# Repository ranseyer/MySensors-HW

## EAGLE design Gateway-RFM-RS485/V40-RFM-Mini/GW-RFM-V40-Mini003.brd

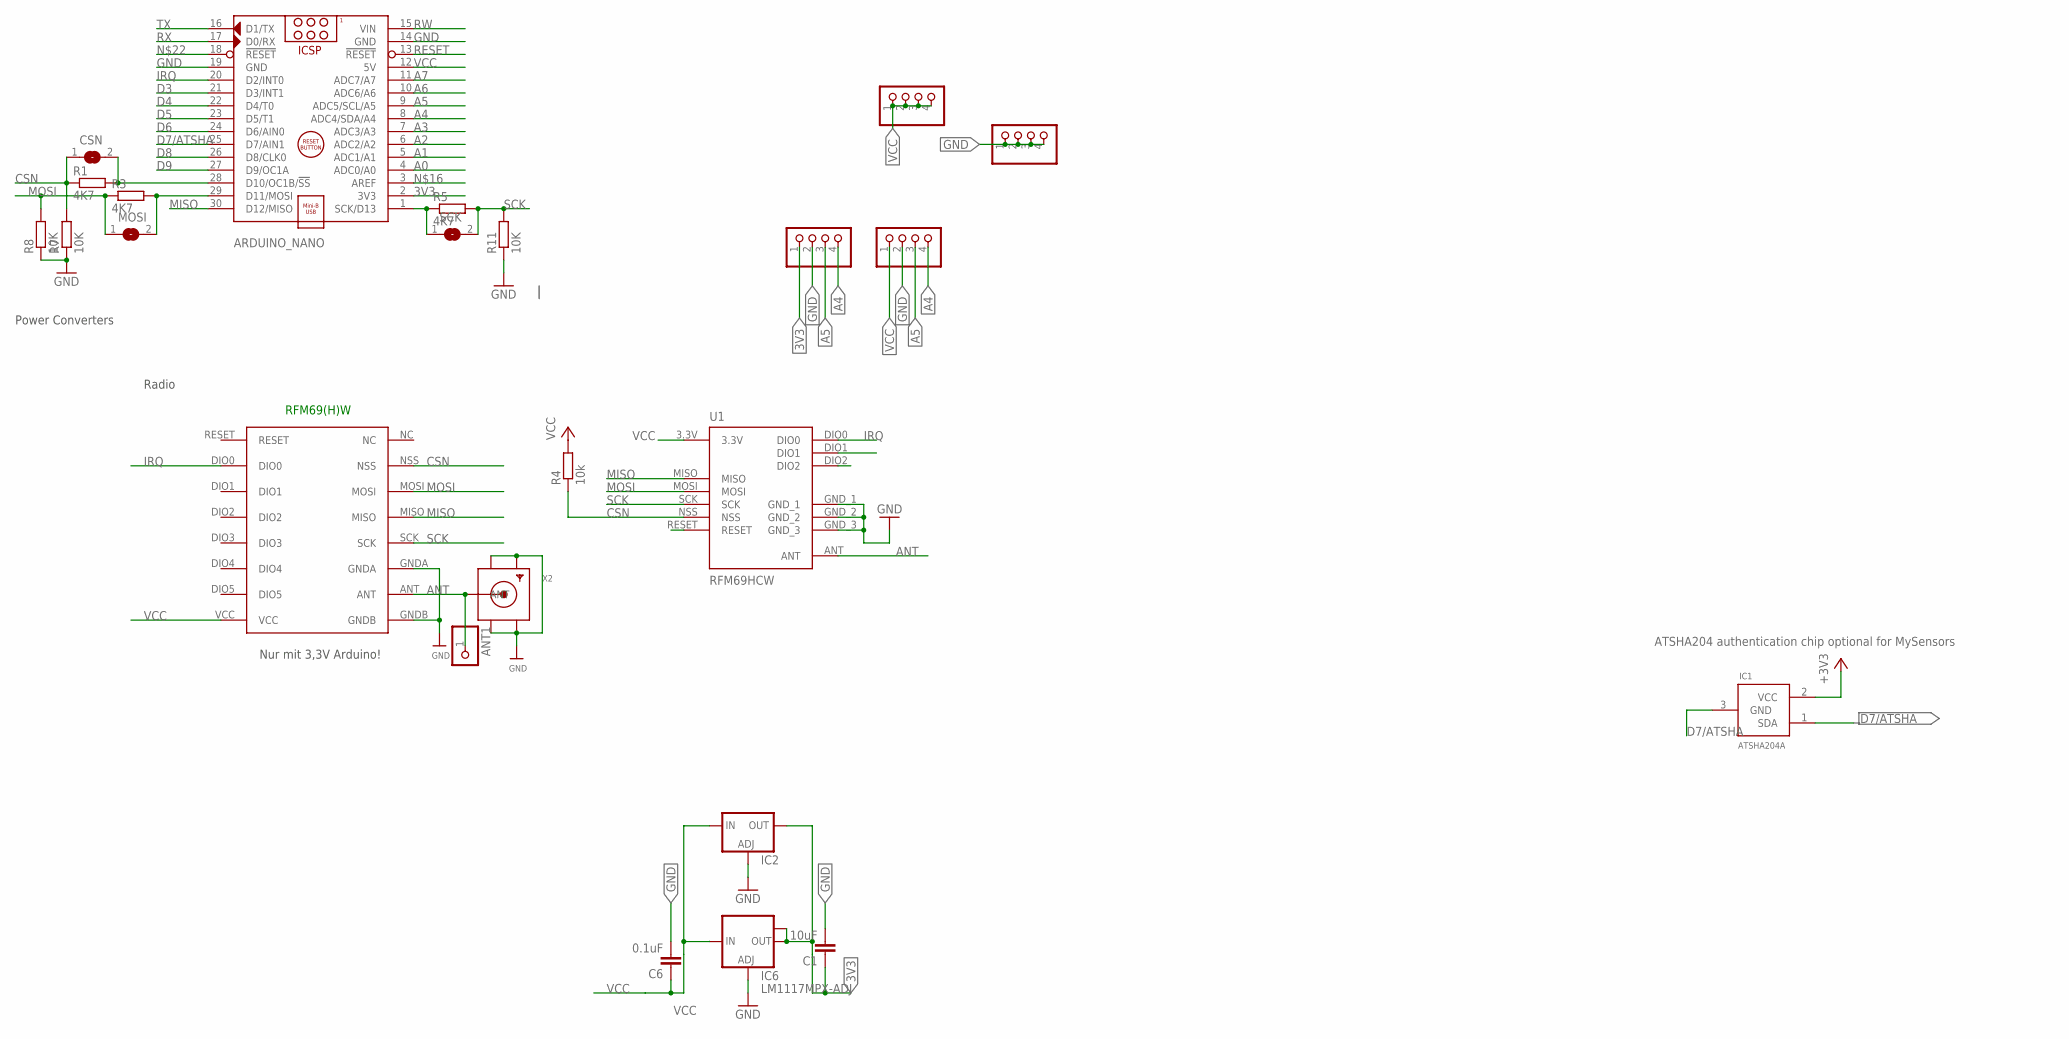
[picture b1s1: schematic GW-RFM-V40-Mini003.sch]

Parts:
ANT1: PINHD-1X1; 1X01
ARDUINO_NANO: ARDUINO_NANO_OHNE-BOHR; ARDUINO_NANO
C1: 10uF; C1210
C6: 0.1uF; C1206
CSN: SJ
IC1: ATSHA204A; SOT23
IC2: LD117ADT50TR; DPACK
IC6: LM1117MPX-ADJ; SOT223
JP1, JP3, JP17, JP18: PINHD-1X04_2.54-S; 1X04-S
MOSI: SJ
R1, R3, R5: 4K7; M0805
R4: 10k; M0805
R7, R8, R11: 10K; M0805
RFM69W: RFM69HW; RFM
SCK: SJ
U1: RFM69HCW; RFM69HCW-XXXS2
X2: SMACONNECTOR_EDGE; SMA_EDGELAUNCH

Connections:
3V3: ARDUINO_NANO.2 (3V3), C1.1, IC2.4 (OUT), IC6.2 (OUT), IC6.TAB (OUT1), JP17.1
A0: ARDUINO_NANO.4 (ADC0/A0)
A1: ARDUINO_NANO.5 (ADC1/A1)
A2: ARDUINO_NANO.6 (ADC2/A2)
A3: ARDUINO_NANO.7 (ADC3/A3)
A4: ARDUINO_NANO.8 (ADC4/SDA/A4), JP17.4, JP18.4
A5: ARDUINO_NANO.9 (ADC5/SCL/A5), JP17.3, JP18.3
A6: ARDUINO_NANO.10 (ADC6/A6)
A7: ARDUINO_NANO.11 (ADC7/A7)
ANT: ANT1.1, RFM69W.ANT, U1.ANT, X2.P (ANT)
CSN: CSN.1, R1.1, R4.1, R7.2, RFM69W.NSS, U1.NSS
D3: ARDUINO_NANO.21 (D3/INT1)
D4: ARDUINO_NANO.22 (D4/T0)
D5: ARDUINO_NANO.23 (D5/T1)
D6: ARDUINO_NANO.24 (D6/AIN0)
D7/ATSHA: ARDUINO_NANO.25 (D7/AIN1), IC1.1 (SDA), IC1.3 (GND)
D8: ARDUINO_NANO.26 (D8/CLK0)
D9: ARDUINO_NANO.27 (D9/OC1A)
GND: ARDUINO_NANO.14 (GND), ARDUINO_NANO.19 (GND), C1.2, C6.2, IC2.1 (ADJ), IC6.1 (ADJ), JP1.1, JP1.2, JP1.3, JP1.4, JP17.2, JP18.2, R7.1, R8.1, R11.1, RFM69W.GNDA, RFM69W.GNDB, U1.GND_1, U1.GND_2, U1.GND_3, X2.GND@1 (GND4), X2.GND@2 (GND3), X2.GND@3 (GND2), X2.GND@4 (GND1)
IRQ: ARDUINO_NANO.20 (D2/INT0), RFM69W.DIO0, U1.DIO0
MISO: ARDUINO_NANO.30 (D12/MISO), RFM69W.MISO, U1.MISO
MOSI: MOSI.1, R3.1, R8.2, RFM69W.MOSI, U1.MOSI
unnamed: ARDUINO_NANO.1 (SCK/D13), R5.1, SCK.1
unnamed: ARDUINO_NANO.28 (D10/OC1B/!SS), CSN.2, R1.2
unnamed: ARDUINO_NANO.29 (D11/MOSI), MOSI.2, R3.2
RESET: ARDUINO_NANO.13 (!RESET)
RW: ARDUINO_NANO.15 (VIN)
RX: ARDUINO_NANO.17 (D0/RX)
SCK: R5.2, R11.2, RFM69W.SCK, SCK.2, U1.SCK
TX: ARDUINO_NANO.16 (D1/TX)
VCC: ARDUINO_NANO.12 (5V), C6.1, IC1.2 (VCC), IC2.3 (IN), IC6.3 (IN), JP3.1, JP3.2, JP3.3, JP3.4, JP18.1, R4.2, RFM69W.VCC, U1.3.3V

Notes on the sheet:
RFM69(H)W
Nur mit 3,3V Arduino!
Radio
ATSHA204 authentication chip optional for MySensors
Power Converters

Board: 2 copper layers, 24 parts (17 on the bottom side), 15 nets, no tracks yet.

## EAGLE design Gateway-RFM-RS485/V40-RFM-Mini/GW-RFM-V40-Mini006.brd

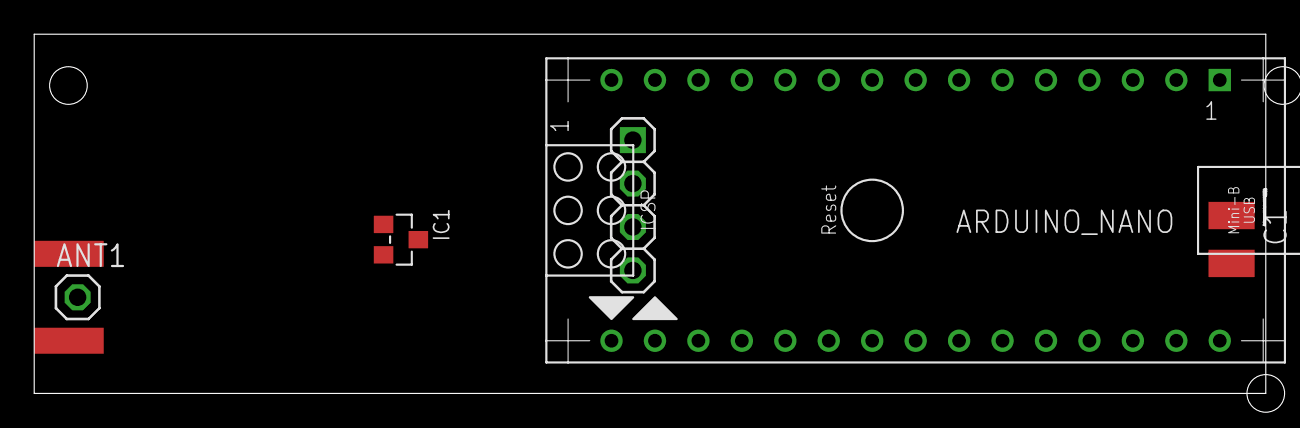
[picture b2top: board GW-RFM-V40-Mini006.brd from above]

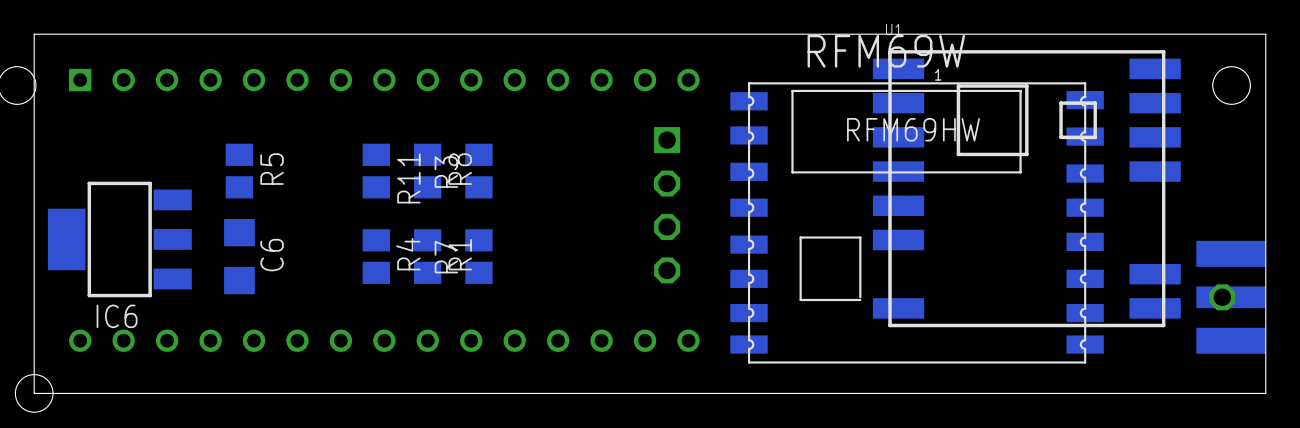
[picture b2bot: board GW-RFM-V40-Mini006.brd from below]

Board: 2 copper layers, 72.0 x 21.0 mm, 17 parts (12 on the bottom side), 15 nets, no tracks yet.

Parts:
ANT1: 1X01
ARDUINO_NANO: ARDUINO_NANO
C1: 10uF; C1210
C6: 0.1uF; C1206
IC1: ATSHA204A; SOT23
IC6: LM1117MPX-ADJ; SOT223
JP17: 1X04-S
R1, R3, R5: 4K7; M0805
R4: 10k; M0805
R7, R8, R11: 10K; M0805
RFM69W: RFM69HW; RFM
U1: RFM69HCW; RFM69HCW-XXXS2
X2: SMA_EDGELAUNCH

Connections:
3V3: ARDUINO_NANO.2, C1.1, IC6.2, IC6.TAB, JP17.1
A4: ARDUINO_NANO.8, JP17.4
A5: ARDUINO_NANO.9, JP17.3
ANT: ANT1.1, RFM69W.ANT, U1.ANT, X2.P
CSN: R1.1, R4.1, R7.2, RFM69W.NSS, U1.NSS
D7/ATSHA: ARDUINO_NANO.25, IC1.1, IC1.3
GND: ARDUINO_NANO.14, ARDUINO_NANO.19, C1.2, C6.2, IC6.1, JP17.2, R7.1, R8.1, R11.1, RFM69W.GNDA, RFM69W.GNDB, U1.GND_1, U1.GND_2, U1.GND_3, X2.GND@1, X2.GND@2, X2.GND@3, X2.GND@4
IRQ: ARDUINO_NANO.20, RFM69W.DIO0, U1.DIO0
MISO: ARDUINO_NANO.30, RFM69W.MISO, U1.MISO
MOSI: R3.1, R8.2, RFM69W.MOSI, U1.MOSI
unnamed: ARDUINO_NANO.1, R5.1
unnamed: ARDUINO_NANO.28, R1.2
unnamed: ARDUINO_NANO.29, R3.2
SCK: R5.2, R11.2, RFM69W.SCK, U1.SCK
VCC: ARDUINO_NANO.12, C6.1, IC1.2, IC6.3, R4.2, RFM69W.VCC, U1.3.3V

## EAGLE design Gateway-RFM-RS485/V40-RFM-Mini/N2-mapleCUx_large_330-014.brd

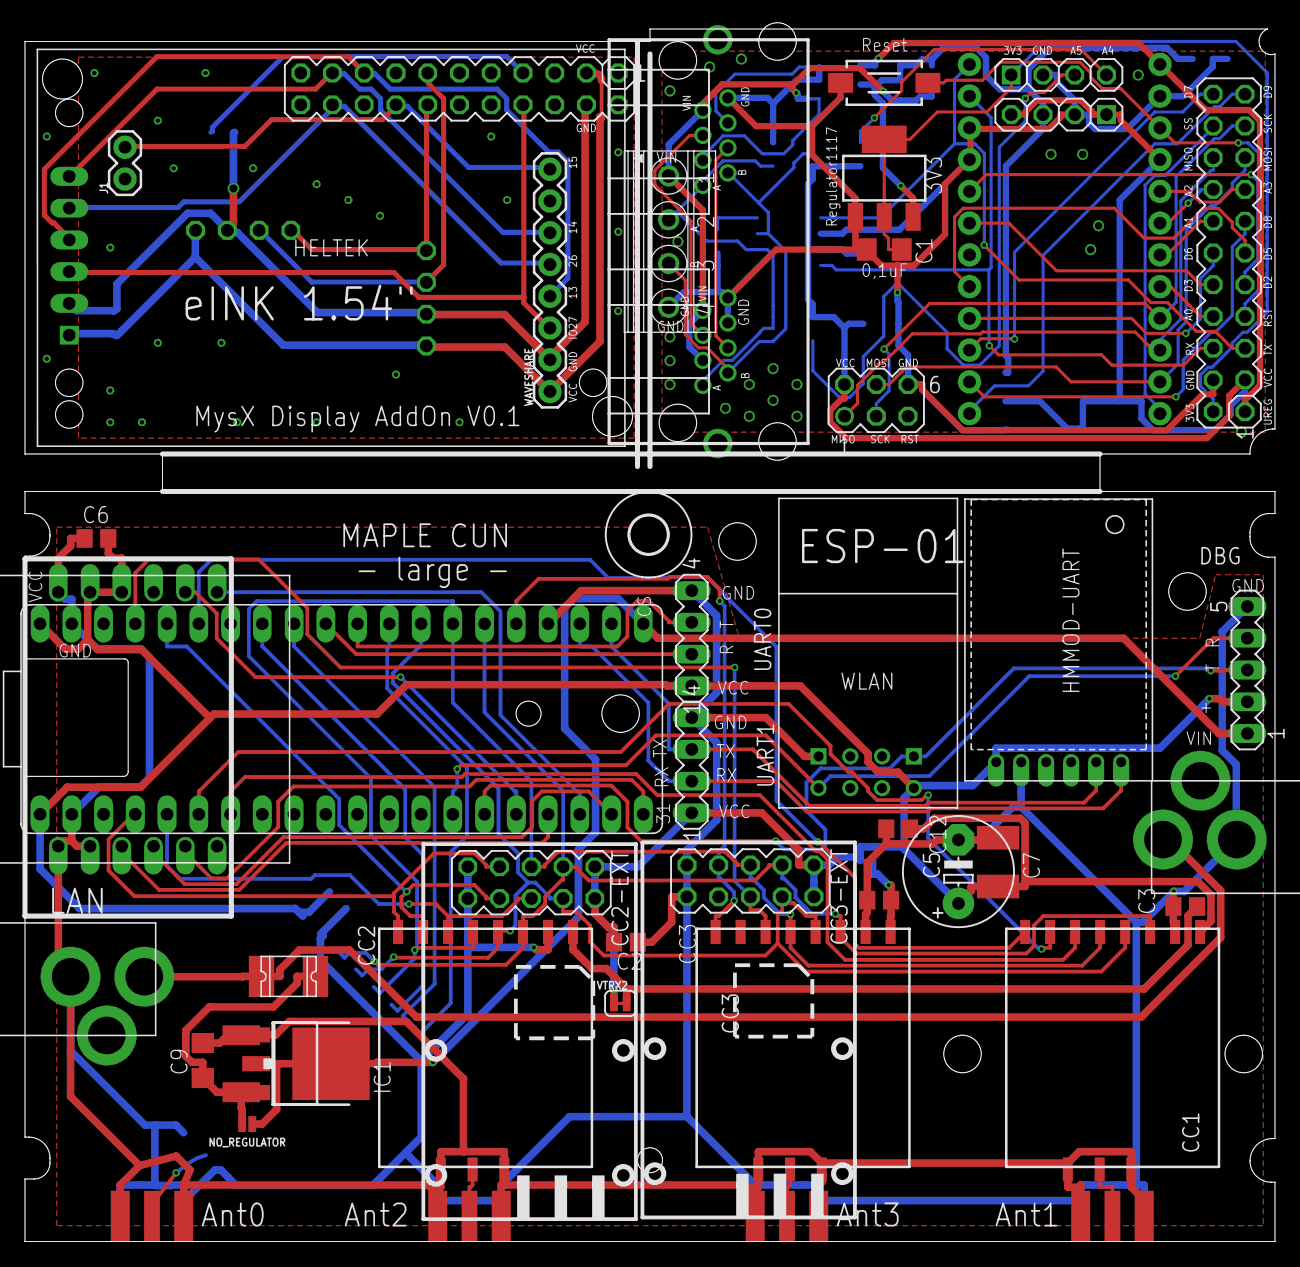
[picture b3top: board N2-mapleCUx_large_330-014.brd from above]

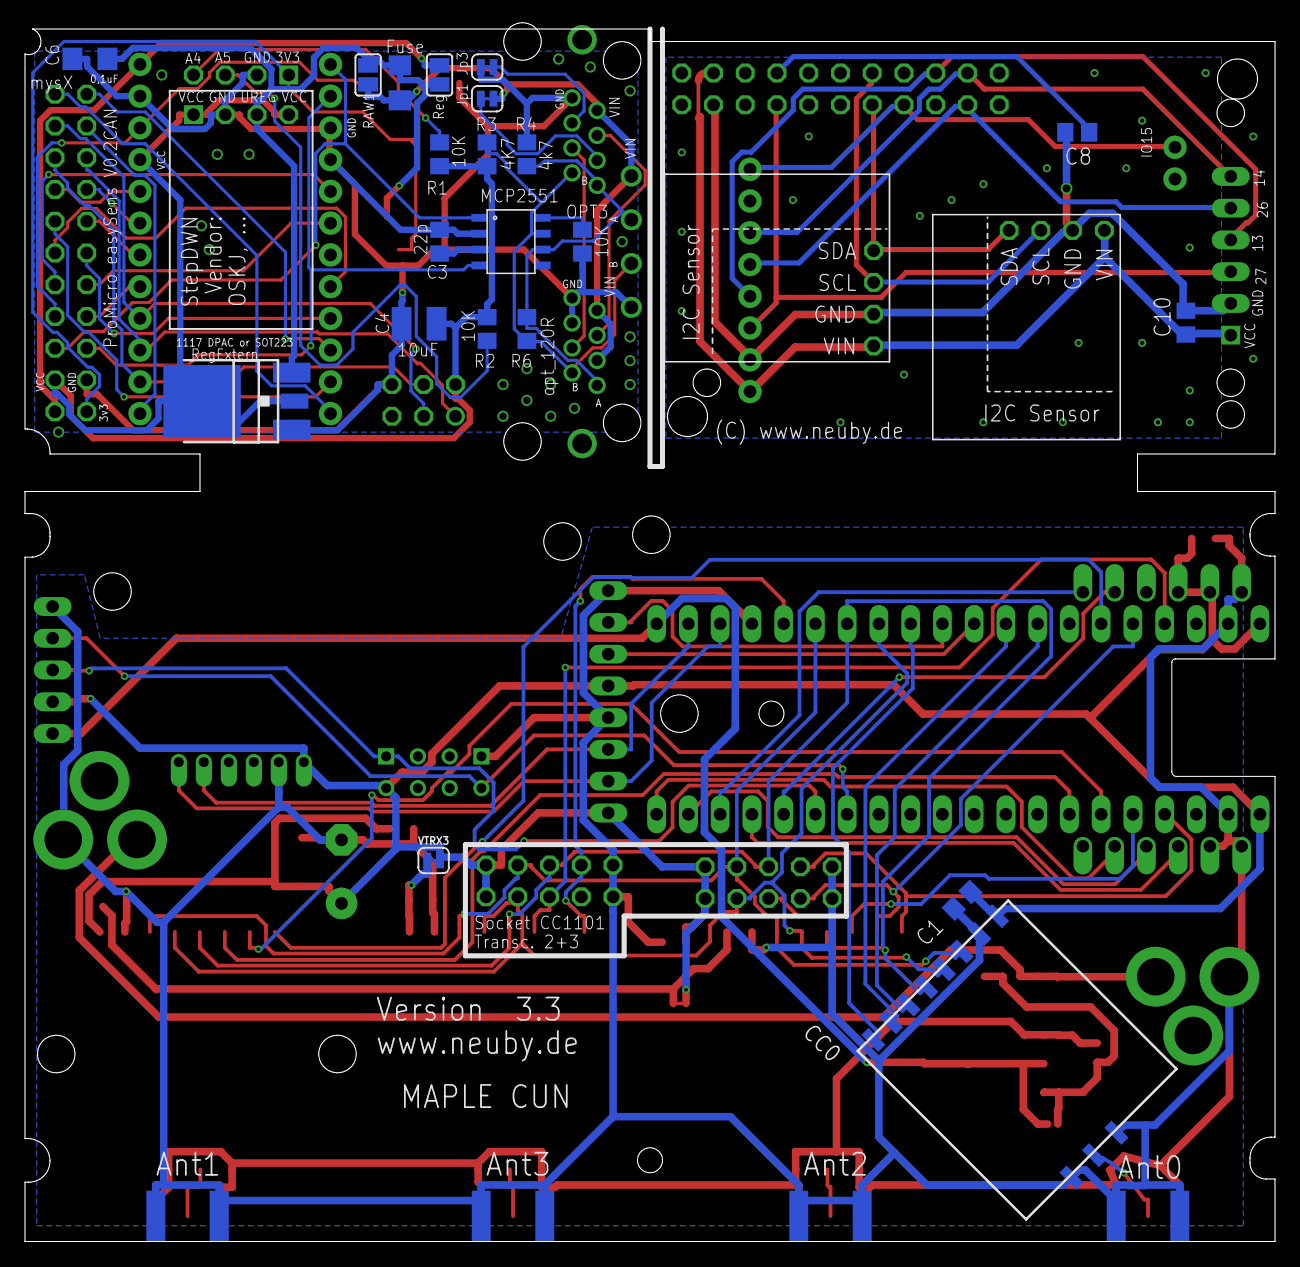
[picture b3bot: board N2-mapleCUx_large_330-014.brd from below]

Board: 2 copper layers, 100.0 x 97.0 mm, 70 parts (24 on the bottom side), 79 nets.

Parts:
B1: SPARKFUN_PRO_MICRO
C1, C2, C3, C4, C6, C12: 22pF; C0805
C5: 220uF; E5-8,5
C7: C1812
C8: 2u2; C0805
C9, C14, C15: 0.1uF; C1206
C10: 22u; C0805
C11: 22p; C0805
C13: 10uF; C1210
CC0: CC1101; CC1101_MODULE1_SMD
CC1, CC2, CC3: CC1101_MODULE1SMD; CC1101_MODULE1_SMD
CC2-EXT, CC3-EXT: CC1101_MODULE3_DIL
DBG: MA05-1
F1: 1812L
F2: 6V/0.75A; 1206
FLASH: DTSM-3
H6: MOUNT-HOLE3.0; 3,0
HELTEK: HELTEC_1.54STANDARD1; HELTEC_1.54INCH
HMMOD-UART: HM-MOD-UARTDIL; HM-MOD-UART-DIL
I2C: 1X04-S
IC1, IC3: LD117ADT50TR; DPACK
IC2: LAN-USR-ES1; USR-ES1
IC4, IC5, IC6: LM1117MPX-ADJ; SOT223
J1: 1X02
J4: RJ45_2X_S
JP1, JP3: JUMPER-SMT_2_NC_TRACE_SILK; SMT-JUMPER_2_NC_TRACE_SILK
MYSX: MA11-2
NO_REGULATOR: JUMPER-SMT_2_NC_PASTE_NO-SILK; SMT-JUMPER_2_NC_PASTE_NO-SILK
OPT3: 10K; R0805
R1, R2: 10K; R0805
R3: 4K7; R0805
R4: 4k7; R0805
R6: 120R; R0805
RAW1: SJ
REG_BRIDGE: SJ
STEPDWN: 1X04-S
SV1: MA03-2
SV2: MA11-2
U$1: MAPLEMINI; 20-DIP
U$2, U$3: 2.1MMJACKTHM; PJ-102A
U$4, U$5: I2C-BREAKOUT; I2C_BREAKOUT
U$6: MCP2551; SOIC-8
UART0, UART1: MA04-1
VTRX2, VTRX3: JUMPER-SMT_2_NC_TRACE_SILK; SMT-JUMPER_2_NC_TRACE_SILK
WAVESHARE: 1X08
WLAN: ESP01
X1, X2, X3, X5: SMA_EDGELAUNCH
X4: 1751264

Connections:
1: J4.1-3, JP1.1
2: J4.1-6, JP3.1
3V1: C15.2, I2C.1, IC5.2, IC5.TAB, SV2.2
A: J4.1-1, J4.2-1, R4.1, R6.2, U$6.CANL, X4.2
A0: B1.17, SV2.8
A1: B1.18, SV2.14
A2: B1.19, SV2.16
A3: B1.20, SV2.15
A4: I2C.4, R1.2
A5: I2C.3, R2.2
ANT0: CC0.ANT, X5.P
ANT1: CC1.ANT, X1.P
ANT2: CC2.ANT, X2.P
ANT3: CC3.ANT, X3.P
B: J4.1-2, J4.2-2, R3.2, R6.1, U$6.CANH, X4.3
CANH: J4.1-4, J4.2-4
CANL: J4.1-5, J4.2-5
CC_CS0: CC0.CSN, U$1.29
CC_CS1: CC1.CSN, U$1.35
CC_CS2: CC2.CSN, CC2-EXT.CSN, U$1.4
CC_CS3: CC3.CSN, CC3-EXT.CSN, U$1.25
CC_IN_0: CC0.GDO2, U$1.33
CC_IN_1: CC1.GDO2, U$1.7
CC_IN_2: CC2.GDO2, CC2-EXT.GDO2, U$1.5
CC_IN_3: CC3.GDO2, CC3-EXT.GDO2, U$1.37
CC_OUT_0: CC0.GDO0, U$1.32
CC_OUT_1: CC1.GDO0, U$1.6
CC_OUT_2: CC2.GDO0, CC2-EXT.GDO0, U$1.36
D2: B1.5, SV2.9
D3: B1.6, SV2.10
D5: B1.8, SV2.11
D6: B1.9, SV2.12
D7: B1.10, SV2.22
D8: B1.11, SV2.13
D9: B1.12, SV2.21
D10_SS: B1.13, SV2.20
D11_MOSI: B1.14, SV1.4, SV2.17
D12_MISO: B1.15, SV1.1, SV2.18
D13_SCK: B1.16, SV1.3, SV2.19
EN: C8.1, MYSX.7
GND: C1.1, C2.1, C3.1, C4.1, C5.-, C6.2, C7.1, C9.2, C12.2, CC0.GND@0, CC0.GND@1, CC0.GND@2, CC1.GND@0, CC1.GND@1, CC1.GND@2, CC2.GND@0, CC2.GND@1, CC2.GND@2, CC2-EXT.GND@0, CC2-EXT.GND@1, CC3.GND@0, CC3.GND@1, CC3.GND@2, CC3-EXT.GND@0, CC3-EXT.GND@1, DBG.5, HMMOD-UART.2, IC1.1, IC2.1, IC2.2, IC2.12, IC6.1, U$1.2, U$1.24, U$1.39, U$2.RING, U$3.RING, UART0.4, UART1.4, WLAN.GND, X1.GND@1, X1.GND@2, X1.GND@3, X1.GND@4, X2.GND@1, X2.GND@2, X2.GND@3, X2.GND@4, X3.GND@1, X3.GND@2, X3.GND@3, X3.GND@4, X5.GND@1, X5.GND@2, X5.GND@3, X5.GND@4
GND1: C8.2, C10.2, HELTEK.GND, MYSX.4, U$4.GND, U$5.GND, WAVESHARE.2
GND2: B1.3, B1.4, B1.23, C11.1, C13.2, C14.2, C15.1, FLASH.1, I2C.2, IC3.1, IC4.1, IC5.1, J4.1-8, J4.2-6, J4.2-8, JP3.2, OPT3.1, R4.2, STEPDWN.2, SV1.6, SV2.4, U$6.VSS, X4.4
IN: C9.1, F1.P$1, IC1.3, IC6.3, NO_REGULATOR.2
IN1: F2.2, J4.1-7, J4.2-3, J4.2-7, JP1.2, RAW1.1, X4.1
IO13: HELTEK.SDI, MYSX.17, WAVESHARE.4
IO14: HELTEK.CLK, MYSX.19, WAVESHARE.6
IO15: J1.2, MYSX.16, WAVESHARE.8
IO21: MYSX.14, U$4.SDA, U$5.SDA
IO22: MYSX.13, U$4.SCL, U$5.SCL
IO26: HELTEK.CS, MYSX.20, WAVESHARE.5
IO27: HELTEK.D/C, MYSX.8, WAVESHARE.3
MISO1: CC0.MISO, CC1.MISO, CC2.MISO, CC2-EXT.MISO, CC3.MISO, CC3-EXT.MISO, U$1.27
MISO2: IC2.7, U$1.18
MOSI1: CC0.MOSI, CC1.MOSI, CC2.MOSI, CC2-EXT.MOSI, CC3.MOSI, CC3-EXT.MOSI, U$1.26
unnamed: C3.2, CC2.VCC, VTRX2.2
unnamed: C4.2, CC3.VCC, VTRX3.2
RESET: B1.22, FLASH.2, SV2.7
RS: OPT3.2, U$6.RS
RST: IC2.3, U$1.17
RX0: B1.2, SV2.6, U$6.RXD
RX1: HMMOD-UART.5, U$1.22, UART1.3
RX-MAPLE: U$1.30, UART0.3
RX_DBG: DBG.4, U$1.14, WLAN.TX
SCK1: CC0.SCLK, CC1.SCLK, CC2.SCLK, CC2-EXT.SCK, CC3.SCLK, CC3-EXT.SCK, U$1.28
SCK2: IC2.4, U$1.19
TX1: HMMOD-UART.6, U$1.23, UART1.2
TX2: B1.1, SV2.5, U$6.TXD
TX-MAPLE: U$1.31, UART0.2
TX_DBG: DBG.3, U$1.15, WLAN.RX
UIN: C14.1, F2.1, IC3.3, IC4.3, IC5.3, RAW1.2, REG_BRIDGE.1, STEPDWN.3
UREG1: B1.24, REG_BRIDGE.2, SV2.1
VCC: C1.2, C2.2, C5.+, C6.1, C7.2, C12.1, CC0.VCC, CC1.VCC, CC2-EXT.VCC@0, CC2-EXT.VCC@1, CC3-EXT.VCC@0, CC3-EXT.VCC@1, DBG.2, HMMOD-UART.1, IC2.10, IC2.11, U$1.1, U$1.40, UART0.1, UART1.1, VTRX2.1, VTRX3.1, WLAN.VCC
VCC1: C10.1, HELTEK.VCC, MYSX.3, U$4.VIN, U$5.VIN, WAVESHARE.1
VCC2: B1.21, C11.2, C13.1, IC3.4, IC4.2, IC4.TAB, R1.1, R2.1, R3.1, STEPDWN.1, STEPDWN.4, SV1.2, SV2.3, U$6.VDD
VIN: F1.P$2, U$2.TIP, U$3.TIP
VIN2: DBG.1, IC1.4, IC6.2, IC6.TAB, NO_REGULATOR.1, U$1.21
WIZ_CS: IC2.5, U$1.20
WIZ_RST: IC2.8, U$1.16

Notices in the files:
parts and their libraries:
microbuilder: This work is placed in the public domain, and may be freely used for commercial and non-commercial work with the following conditions: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
SparkFun-Jumpers: Licensing: Creative Commons ShareAlike 4.0 International - https://creativecommons.org/licenses/by-sa/4.0
